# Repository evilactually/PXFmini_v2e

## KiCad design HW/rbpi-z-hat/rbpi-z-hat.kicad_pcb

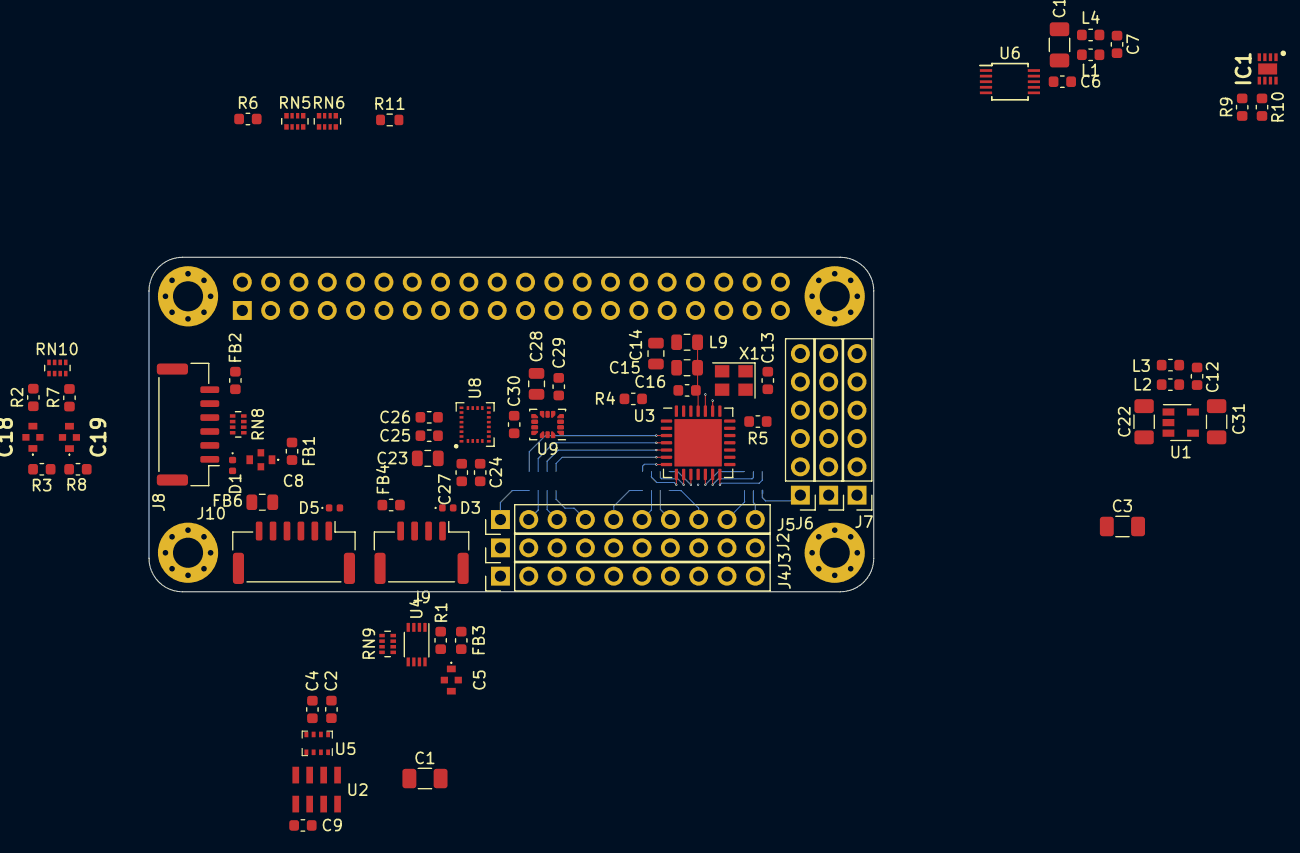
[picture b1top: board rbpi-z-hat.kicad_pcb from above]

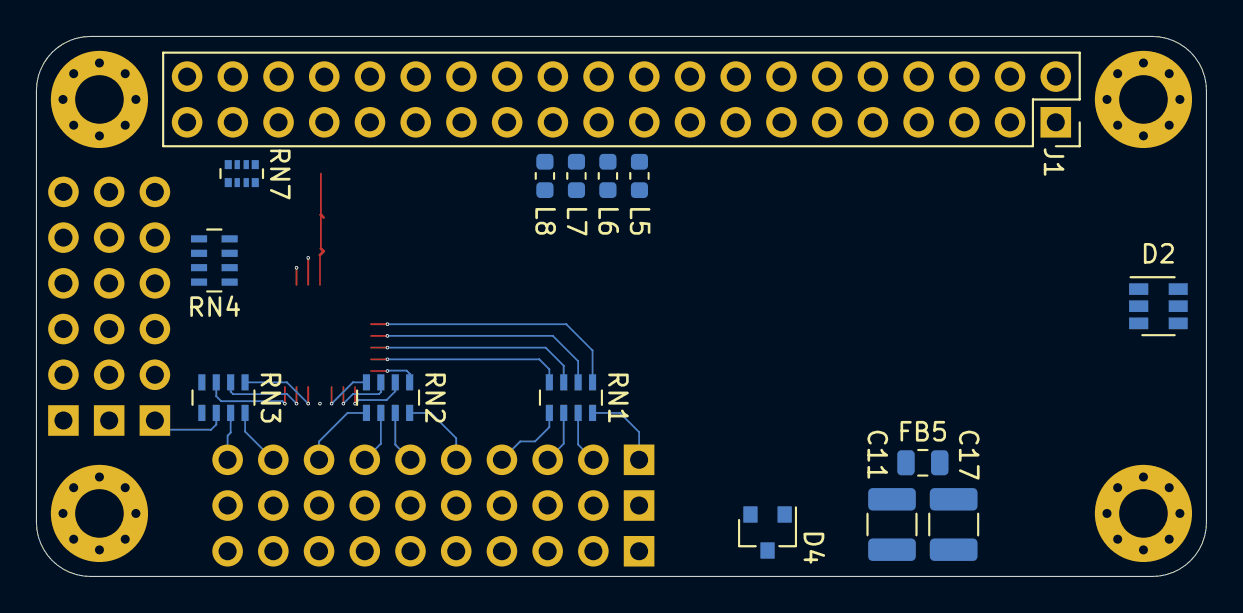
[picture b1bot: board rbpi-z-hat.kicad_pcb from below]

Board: 4 copper layers, 65.0 x 30.0 mm, 94 parts (15 on the bottom side), 90 nets.

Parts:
C1, C3, C10, C22, C31: 22uF/10V; C_1206_3216Metric
C2, C4, C7, C9, C12: 100nF; C_0603_1608Metric
C5, C8: 1uF/16V/0805/NFM21PC105B1C3D; NFM21PC105B1C3D
C6, C13, C16, C24, C25, C27, C30: 0.1uF; C_0603_1608Metric
C11, C17: 22uF/16V; C_1210_3225Metric
C14, C15: 10uF; C_0805_2012Metric
C18, C19: 1uF/16V/NFM21PC105B1C3D; NFM21PC105B1C3D
C23: 4.7uF/10V; C_0805_2012Metric
C26: 10nF/16V; C_0603_1608Metric
C28: 4.7uF; C_0805_2012Metric
C29: 10nF; C_0603_1608Metric
D1, D3, D5: PESD0402-140; D_0402_1005Metric
D2: ESDA5V3SC5; SOT-23-6
D4: PESD3V3S2UT; SOT-23
FB1, FB2, FB3, FB4: Ferrite_Bead; L_0603_1608Metric
FB5, FB6: MPZ2012S221AT000; L_0805_2012Metric
IC1: BQ24315DSGR; SON50P200X200X80-9N
J1: RBPI_CONN; PinSocket_2x20_P2.54mm_Vertical
J2, J3, J4: Conn_01x10; PinHeader_1x10_P2.54mm_Vertical
J5, J6, J7: Conn_01x06; PinHeader_1x06_P2.54mm_Vertical
J8: Conn_01x06_MountingPin; JST_GH_BM06B-GHS-TBT_1x06-1MP_P1.25mm_Vertical
J9: JST_GH; JST_GH_BM04B-GHS-TBT_1x04-1MP_P1.25mm_Vertical
J10: JST_GH; JST_GH_BM06B-GHS-TBT_1x06-1MP_P1.25mm_Vertical
L1, L2, L3, L4, L5, L6, L7, L8: Ferrite_Bead; L_0603_1608Metric
L9: Ferrite_Bead; L_0805_2012Metric
MH1, MH2, MH3, MH4: M2.5; MountingHole_2.7mm_M2.5_Pad_Via
R1: 200K; R_0603_1608Metric
R2, R7: 10K/0.1%; L_0603_1608Metric
R3, R8: 1M; L_0603_1608Metric
R4, R5, R9, R11: 10K; R_0603_1608Metric
R6: 47K; R_0603_1608Metric
R10: 25K; R_0603_1608Metric
RN1, RN2, RN3, RN4: 220R; R_Array_Concave_4x0603
RN5, RN6, RN7: 10K/4x0402; R_Array_Convex_4x0402
RN8: 120R; R_Array_Concave_4x0402
RN9: 1K5; R_Array_Concave_4x0402
RN10: 10K/1%; R_Array_Concave_4x0402
U1: MIC5504-3.3YM5; SOT-23-5
U2: MS5611
U3: PCA9685BS; QFN-28-1EP_6x6mm_P0.65mm_EP4.25x4.25mm
U4: PCA9306DC; VSSOP-8_2.3x2mm_P0.5mm
U5: BMP280; Bosch_LGA-8_2x2.5mm_P0.65mm_ClockwisePinNumbering
U6: ADS1015IDGS; TSSOP-10_3x3mm_P0.5mm
U8: LSM9DS1; LGA-24L_3x3.5mm_P0.43mm
U9: ICM-42688-P; LGA-14_3x2.5mm_P0.5mm_LayoutBorder3x4y
X1: ASEMB-25.000MHZ-LC-T; Oscillator_SMD_Abracon_ASE-4Pin_3.2x2.5mm

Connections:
+3V3: C7.1, C14.1, J1.1, J1.17, L1.1, L9.1, R1.2, R11.1, RN5.5 (R4.2), RN5.6 (R3.2), RN5.7 (R2.2), RN5.8 (R1.2), RN6.5 (R4.2), RN6.7 (R2.2), RN6.8 (R1.2), RN7.5 (R4.2), RN7.6 (R3.2), RN7.7 (R2.2), RN7.8 (R1.2), RN9.5 (R4.2), RN9.6 (R3.2), RN9.7 (R2.2), RN9.8 (R1.2), U4.1 (VREF1)
+5V: FB1.2, FB3.2, J1.2, J1.4
/ADS1015/ADS_GND: C6.1, C10.2, L4.2, U6.1 (ADDR), U6.3 (GND)
/ADS1015/ADS_VDD: C6.2, C10.1, L1.2, U6.8 (VDD)
/BARO/BARO_MS_nCS: U2.4 (CSB), U2.5 (CSB)
/BMP_nCS: J1.26, R11.2, U5.2 (CSB)
/BQ24313/BQ_IN: C17.1, FB5.1, IC1.1 (IN)
/BQ24313/BQ_nCE: IC1.5 (~CE), R9.1
/BQ24313_OUT: C12.1, IC1.8 (OUT), L2.1
/CUR_SENS: RN10.5 (R4.2), RN10.8 (R1.2), U6.4 (AIN0)
/LSM_nCS: J1.24, RN7.4 (R4.1), U8.7 (CS_A/G), U8.8 (CS_M)
/PCA9685/PCA_EXTCLK: U3.22 (EXTCLK), X1.3 (OUT)
/PCA9685/PCA_VDD: C13.1, C15.1, C16.1, L9.2, R5.1, U3.25 (VDD), X1.4 (Vdd)
/PCA9685/PWM_0: J2.1, RN1.8 (R1.2)
/PCA9685/PWM_1: J2.2, RN1.7 (R2.2)
/PCA9685/PWM_2: J2.3, RN1.6 (R3.2)
/PCA9685/PWM_3: J2.4, RN1.5 (R4.2)
/PCA9685/PWM_4: J2.5, RN2.8 (R1.2)
/PCA9685/PWM_5: J2.6, RN2.7 (R2.2)
/PCA9685/PWM_6: J2.7, RN2.6 (R3.2)
/PCA9685/PWM_7: J2.8, RN2.5 (R4.2)
/PCA9685/PWM_8: J2.9, RN3.8 (R1.2)
/PCA9685/PWM_9: J2.10, RN3.7 (R2.2)
/PCA9685/PWM_10: J5.1, RN3.6 (R3.2)
/PCA9685/PWM_11: J5.2, RN3.5 (R4.2)
/PCA9685/PWM_12: J5.3, RN4.8 (R1.2)
/PCA9685/PWM_13: J5.4, RN4.7 (R2.2)
/PCA9685/PWM_14: J5.5, RN4.6 (R3.2)
/PCA9685/PWM_15: J5.6, RN4.5 (R4.2)
/PCA9685/PWM_OUT0: RN1.1 (R1.1), U3.3 (LED0)
/PCA9685/PWM_OUT1: RN1.2 (R2.1), U3.4 (LED1)
/PCA9685/PWM_OUT2: RN1.3 (R3.1), U3.5 (LED2)
/PCA9685/PWM_OUT3: RN1.4 (R4.1), U3.6 (LED3)
/PCA9685/PWM_OUT4: RN2.1 (R1.1), U3.7 (LED4)
/PCA9685/PWM_OUT5: RN2.2 (R2.1), U3.8 (LED5)
/PCA9685/PWM_OUT6: RN2.3 (R3.1), U3.9 (LED6)
/PCA9685/PWM_OUT7: RN2.4 (R4.1), U3.10 (LED7)
/PCA9685/PWM_OUT8: RN3.1 (R1.1), U3.12 (LED8)
/PCA9685/PWM_OUT9: RN3.2 (R2.1), U3.13 (LED9)
/PCA9685/PWM_OUT10: RN3.3 (R3.1), U3.14 (LED10)
/PCA9685/PWM_OUT11: RN3.4 (R4.1), U3.15 (LED11)
/PCA9685/PWM_OUT12: RN4.1 (R1.1), U3.16 (LED12)
/PCA9685/PWM_OUT13: RN4.2 (R2.1), U3.17 (LED13)
/PCA9685/PWM_OUT14: RN4.3 (R3.1), U3.18 (LED14)
/PCA9685/PWM_OUT15: RN4.4 (R4.1), U3.19 (LED15)
/PCA9685/SERVO_POWER: J3.1, J3.2, J3.3, J3.4, J3.5, J3.6, J3.7, J3.8, J3.9, J3.10, J6.1, J6.2, J6.3, J6.4, J6.5, J6.6
/PCA_nOE: R5.2, U3.20 (~OE)
/POWER_CONN/BAT_CUR: C18.1, J10.3, R3.1
/POWER_CONN/BAT_VOLT: C19.1, J10.4, R8.1
/SCL1: J1.3, RN6.1 (R1.1), RN9.4 (R4.1), U3.23 (SCL), U4.2 (SCL1), U6.10 (SCL)
/SDA1: J1.5, RN6.2 (R2.1), RN9.3 (R3.1), U3.24 (SDA), U4.3 (SDA1), U6.9 (SDA)
/SENSORS_POWER/MIC5504/MIC_VIN: C22.1, L2.2, U1.1 (VIN)
/SENS_FGND: C1.2, C2.2, C3.2, C4.2, C9.2, C22.2, C23.2, C24.2, C25.2, C26.2, C27.2, C28.2, C29.2, C30.2, C31.2, L3.2, U1.2 (GND), U2.2 (PS), U2.3 (GND), U5.1 (GND), U5.7 (GND), U8.14 (RES), U8.15 (RES), U8.16 (RES), U8.17 (RES), U8.18 (RES), U8.19 (GND), U8.20 (GND), U9.6 (GND)
/SENS_MISO: L6.1, U2.6 (SDO), U5.5 (SDO), U8.5 (SDO_A/G), U8.6 (SDO_M), U9.1 (AP_SDO)
/SENS_MOSI: L5.1, U2.7 (SDI/SDA), U5.3 (SDI), U8.4 (SDA/SDI/SDO), U9.14 (AP_SDI)
/SENS_SCK: L7.1, U2.8 (SCLK), U5.4 (SCK), U8.2 (SCL/SPC), U9.13 (AP_SCLK)
/SENS_VDD: C1.1, C2.1, C3.1, C4.1, C9.1, C23.1, C24.1, C25.1, C28.1, C29.1, C30.1, C31.1, U1.5 (VOUT), U2.1 (VDD), U5.6 (VDDIO), U5.8 (VDD), U8.1 (VDDIO), U8.3 (VDDIO), U8.22 (VDD), U8.23 (VDD), U9.5 (VDDIO), U9.8 (VDD)
/SPI0_MISO: J1.21, L6.2, RN7.2 (R2.1)
/SPI0_MOSI: J1.19, L5.2, RN7.1 (R1.1)
/SPI0_SCK: J1.23, L7.2, RN7.3 (R3.1)
/UART_CTS: RN5.3 (R3.1), RN8.3 (R3.1)
/UART_RTS: RN5.4 (R4.1), RN8.4 (R4.1)
/UART_RX: J1.10, RN5.1 (R1.1), RN8.2 (R2.1)
/UART_TX: J1.8, RN5.2 (R2.1), RN8.1 (R1.1)
/VOLT_SENS: RN10.6 (R3.2), RN10.7 (R2.2), U6.5 (AIN1)
/rbpi/Pin_7_PPM_SBUS_INPUT: J1.7, R6.1, RN6.3 (R3.1)
GNDD: C5.2, C7.2, C8.2, C11.2, C12.2, C13.2, C14.2, C15.2, C16.2, C17.2, C18.2, C19.2, D1.2 (A2), D2.2 (COM), D2.5 (COM), D3.2 (A2), D4.3 (A), D5.2 (A2), FB2.1, FB4.1, FB6.1, IC1.2 (VSS), IC1.6 (VBAT), IC1.9 (EP), J1.6, J1.9, J1.14, J1.20, J1.25, J1.30, J1.34, J1.39, J4.1, J4.2, J4.3, J4.4, J4.5, J4.6, J4.7, J4.8, J4.9, J4.10, J7.1, J7.2, J7.3, J7.4, J7.5, J7.6, J8.MP (MountPin), J9.MP (MountPin), J10.MP (MountPin), L3.1, L4.1, MH1.1, MH2.1, MH3.1, MH4.1, R3.2, R4.2, R6.2, R8.2, R9.2, R10.2, RN10.3 (R3.1), RN10.4 (R4.1), U3.11 (VSS), U3.29 (VSS), U4.4 (GND), X1.2 (GND)
unnamed: C5.1, FB3.1
unnamed: C8.1, FB1.1
unnamed: C18.3, R2.1
unnamed: C19.3, R7.1
unnamed: C8.3, D1.1 (A1), J8.1
unnamed: D2.1 (TVS1), J8.5, RN8.5 (R4.2)
unnamed: D2.3 (TVS2), J8.4, RN8.6 (R3.2)
unnamed: D2.4 (TVS3), J8.3, RN8.7 (R2.2)
unnamed: D2.6 (TVS4), J8.2, RN8.8 (R1.2)
unnamed: C5.3, D3.1 (A1), J9.1
unnamed: C11.1, D5.1 (A1), FB5.2, J10.1, J10.2
unnamed: IC1.7 (ILIM), R10.1
unnamed: FB2.2, J8.6
unnamed: D4.2 (K), J9.2, RN9.1 (R1.1), U4.6 (SCL2)
unnamed: D4.1 (K), J9.3, RN9.2 (R2.1), U4.5 (SDA2)
unnamed: FB4.2, J9.4
unnamed: FB6.2, J10.5, J10.6
unnamed: R2.2, RN10.1 (R1.1)
unnamed: R7.2, RN10.2 (R2.1)
unnamed: R4.1, U3.1 (A3), U3.2 (A4), U3.21 (A5), U3.26 (A0), U3.27 (A1), U3.28 (A2)
unnamed: R1.1, U4.7 (VREF2), U4.8 (EN)
unnamed: C27.1, U8.24 (C1)
unnamed: C26.1, U8.21 (CAP)

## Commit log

2023-05-08 Routing
